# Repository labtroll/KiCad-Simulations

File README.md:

# Simulation Examples for KiCad 8.0 Using Ngspice

The subfolders contain KiCad 7.99/8.0 projects with schematics containing ngspice simulations, created by [Holger Vogt](https://forum.kicad.info/u/holger), originally published in a [KiCad forum post](https://forum.kicad.info/t/more-simulation-examples-for-kicad-eeschema-ngspice/45546)

:warning: Directories in this repository are named after the original 7z file name and may differ from the xxx.7z folder name and the contained xxx.kicad_pro project file. This should probably be refactored to follow KiCad best practices of naming the folder the same as the contained `.kicad_pro` file. This is, however, not a trivial task, as several of the original 7z archives contain multiple `.kicad_pro` project files.

## FOSDEM 2024 presentation

A number of these circuits were included in a presentation on [FOSDEM 2024](https://fosdem.org/2024/): [ngspice circuit simulator - stand-alone and embedded into KiCad](https://fosdem.org/2024/schedule/event/fosdem-2024-2834-ngspice-circuit-simulator-stand-alone-and-embedded-into-kicad/) ([slides](https://fosdem.org/2024/events/attachments/fosdem-2024-2834-ngspice-circuit-simulator-stand-alone-and-embedded-into-kicad/slides/22676/ngspice-HolgerVogt_tEfhemB.pdf))

## Ngspice User's Manual

For convenience, here are some useful links to ngspice documentation:
* [ngspice User's Manual](https://ngspice.sourceforge.io/docs/ngspice-html-manual/manual.xhtml)
* [Tutorial: ngspice simulation in KiCad/Eeschema](https://ngspice.sourceforge.io/ngspice-eeschema.html)

# Simulation Examples

The new simulator interface in KiCad 8.0 is offering a lot of enhancements, which make it absolutely worthwile to have a look at.

The examples provided should all run out-of-the-box:
1. Locate the project subfolder
2. Open the `*.kicad_pro` project or directly open the schemtic in the `*.kicad_sch` file
3. In the `KiCad Schematic Editor`: `Inspect` :arrow_right: `Simulator` :arrow_right: `Run` (green triangle).

## Simulation Circuits

The circuits shown below are not optimized, but may serve as a good starting point.

* **RC Low Pass Filter**, see [rc-filter](rc-filter)
* **Boost Converter**, see [Boost](Boost)
* **Regulated boost converter**, see [boost-complete](boost-complete)
* **Regulated boost converter**, see [boost-regulated-os](boost-regulated-os)  
  Version which does not need ngspice-42, as it relies on a pwm generator made with the vernerable one-shot code model.  
* **Buck Converter**, see [Buck](Buck)
* **Royer Converter**, see [Royer](Royer)
* **LLC Converter**, see [LLC](LLC)
* **Digital PWM amplifier**, see [pwm-audio](pwm-audio)
* **Digital PWM amplifier update**, see [pwm-audio-2](pwm-audio-2)
* **Another Class-D 2.5 kW audio amplifier**, see [Class-D](Class-D)
* **Analog multiplier**, see [analog-multiplier](analog-multiplier)
* **Generic symbols with generic models**, see [intro4](intro4)
* **IBIS interface simulation**, see [ibis-test](ibis-test)
* **Amplifier with controlled gain, using TI TCA810**, see [gain-ctrl-amp](gain-ctrl-amp)
* **Up-Down Counter**, see [up-down-counter](up-down-counter)
* **Triangle generator with MAX9000**, see [MAX9000](MAX9000)
* **The venerable ICL8038**, see [ICL8038](ICL8038)
* **Generating a negative voltage from a positive supply with LTC1044**, see [LTC1044](LTC1044)
* **Integrated linear amp (LM3886), simple, real, Tian Probe**, see [LM3886-Tian](LM3886-Tian)
* **A bipolar 741 operational amplifier**, see [741](741)
* **Q17, a redesign of the famous QUAD405 High-End Audio Amplifier**, see [Q17](Q17)
* **Quadrature Rotary Encoder (Digital Simulation)**, see [QEI_public_8_mod](QEI_public_8_mod)
* **40106-Based Oscillator**, see [rel_osc](rel_osc)
* **A simple Phase Shift, Single Bipolar Transistor Oscillator**, see [bip-osc-2](bip-osc-2)
* **CMOS555_4**, see [CMOS555_4](CMOS555_4)
* **Full Bridge N-CMOS Circuit**, see [FullBridge](FullBridge)
* **555 Bipolar**, see [555-bipolar](555-bipolar)
* **Pass Labs F5 Turbo V2 thermal simulation**, see [PassLabsF5](PassLabsF5)
* **[Sallen-Key low-pass Filter](sallen-key-lowpass)**
* **[Sallen-Key high-pass Filter](sallen-key-highpass)**

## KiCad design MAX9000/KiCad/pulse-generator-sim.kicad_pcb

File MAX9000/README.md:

## Triangle generator with MAX9000

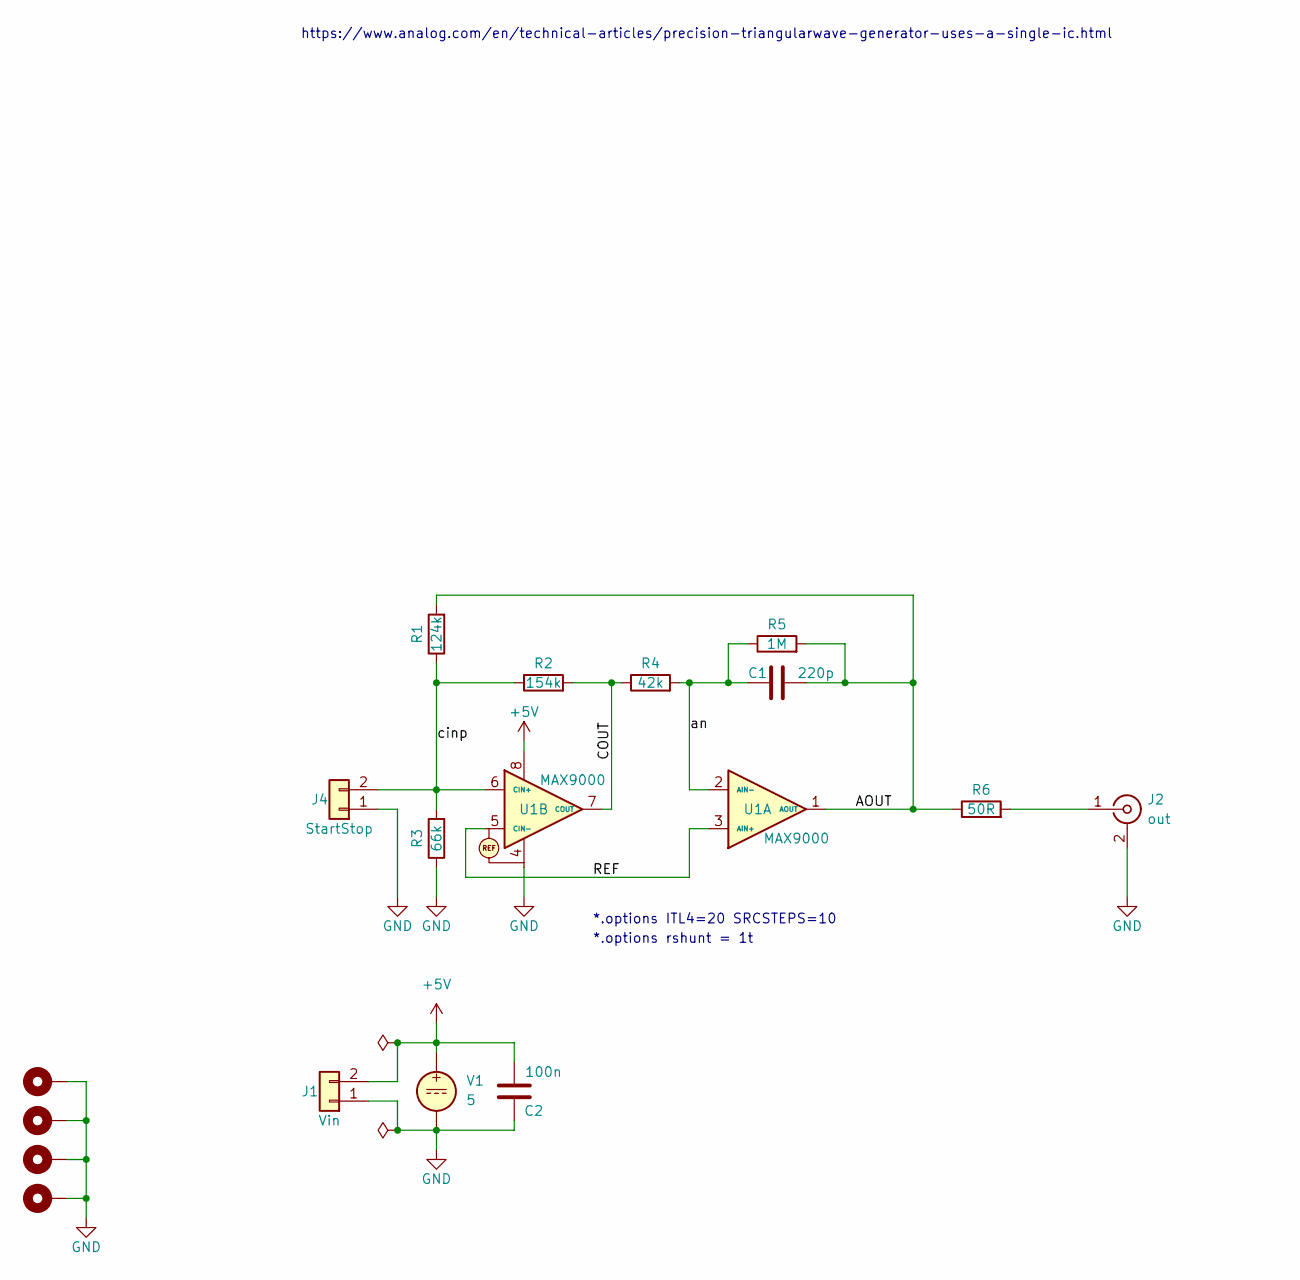
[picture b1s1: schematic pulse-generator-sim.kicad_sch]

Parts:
C1: 220p; C_0805_2012Metric
C2: 100n; C_0805_2012Metric
H1, H2, H3, H4: MountingHole_Pad; MountingHole_3.2mm_M3_DIN965_Pad
J1: Vin; PinHeader_1x02_P2.54mm_Vertical
J2: out; Connector_TE_MCX_1060984-1
J4: StartStop; PinHeader_1x02_P2.54mm_Vertical
R1: 124k; R_0603_1608Metric
R2: 154k; R_0603_1608Metric
R3: 66k; R_0603_1608Metric
R4: 42k; R_0603_1608Metric
R5: 1M; R_0603_1608Metric
R6: 50R; R_0603_1608Metric
U1: MAX9000; MSOP-8_3x3mm_P0.65mm
V1: 5

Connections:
+5V: C2.2, J1.2, U1.8, V1.1
/AOUT: C1.2, R1.2, R5.2, R6.1, U1.1 (AOUT)
/COUT: R2.2, R4.1, U1.7 (COUT)
/REF: U1.3 (AIN+), U1.5 (CIN-)
GND: C2.1, H1.1, H2.1, H3.1, H4.1, J1.1, J2.2 (Ext), J4.1, R3.1, U1.4, V1.2
unnamed: J2.1 (In), R6.2
unnamed: J4.2, R1.1, R2.1, R3.2, U1.6 (CIN+)
unnamed: C1.1, R4.2, R5.1, U1.2 (AIN-)

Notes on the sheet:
*.options rshunt = 1t
*.options ITL4=20 SRCSTEPS=10
https://www.analog.com/en/technical-articles/precision-triangularwave-generator-uses-a-single-ic.html

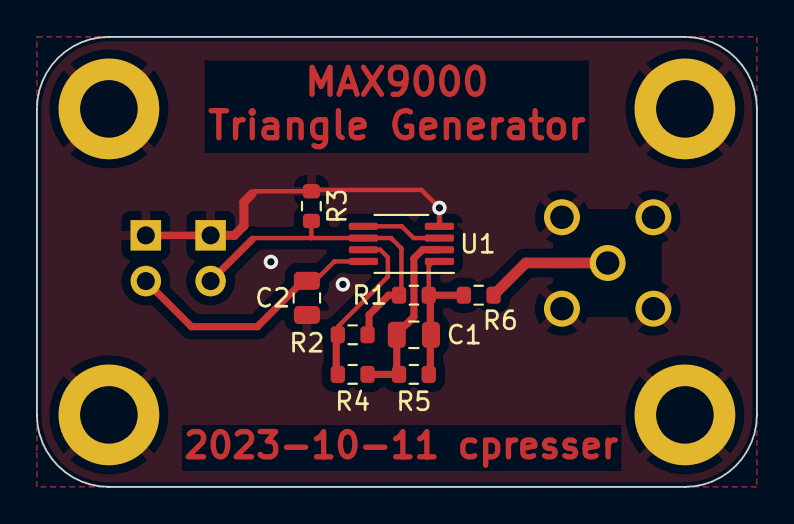
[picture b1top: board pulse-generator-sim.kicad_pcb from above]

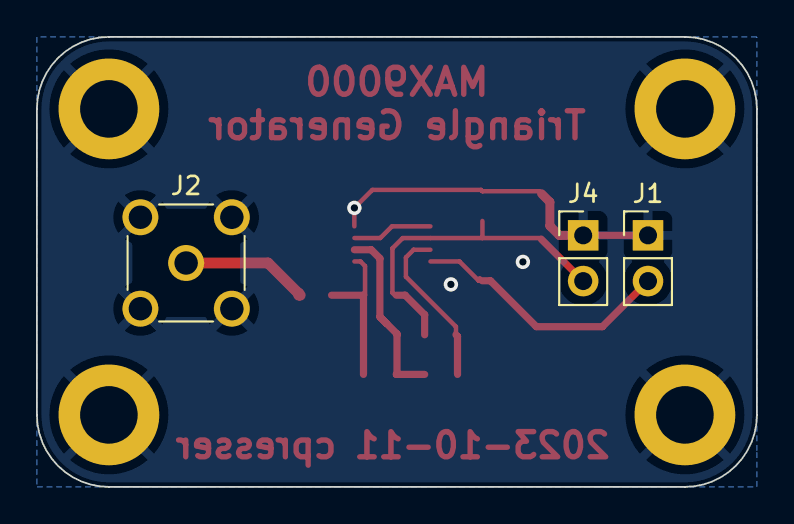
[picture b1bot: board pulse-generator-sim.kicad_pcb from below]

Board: 2 copper layers, 40.0 x 25.0 mm, 16 parts (3 on the bottom side), 8 nets.

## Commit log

2024-02-26 Initial commit of extracted 7z archives
    Including git stuff and README
2024-02-26 New readme
2024-02-26 Update README.md
    images
2024-02-26 Renamed folders and added extra projects
2024-02-26 Added images
2024-02-26 Added content from previous simulations
2024-02-26 Update README.md with previous simulations
2024-02-26 Copied documentation from central README to README in sub projects
2024-02-26 Update README.md
    Removed documentation details from central README file, and present project link list
2024-02-27 Added QEI digital simulation project
2024-02-27 Added QEI
2024-02-27 Added source to QEI readme
2024-02-27 Added Digital Simulation QEI project link
2024-02-27 Update README.md
    Added screenshots from forum post
2024-03-01 Updated QEI project from updated source
    Updated from Holger's source at https://forum.kicad.info/t/more-simulation-examples-for-kicad-eeschema-ngspice/45546/4
2024-03-05 555 Bipolar simulation
2024-03-05 Update README.md with 555-bipolar
2024-03-05 Updated to KiCad 8, changed simulation duration for better plot
2024-03-05 Update README.md with simulation trace
2024-03-05 Create README.md
    contains schematics, transient plot and fft
2024-03-05 Update README.md - added PassLabsF5
2024-03-05 Minor updates to simulations
    Mostly adding legends to plots for inclusion in README files
2024-03-05 Delete README
    Information moved to README.md
2024-03-05 Added Sallen-Key lowpass filter
2024-03-05 Added sallen-key-highpass
2024-03-12 Updated LLC analysis files From Holger's examples at https://forum.kicad.info/t/more-simulation-examples-for-kicad-eeschema-ngspice/45546
2024-03-12 Added simple RC Filter simulation
